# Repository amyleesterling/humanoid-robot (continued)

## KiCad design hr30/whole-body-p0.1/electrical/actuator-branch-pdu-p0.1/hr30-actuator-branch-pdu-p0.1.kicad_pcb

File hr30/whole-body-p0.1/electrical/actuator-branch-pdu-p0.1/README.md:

# HR-30 actuator branch PDU P0.1

**PRELIMINARY - NOT APPROVED FOR PROCUREMENT, FABRICATION, ASSEMBLY, CONNECTION, POWERED TESTING, MOTION OR ENERGIZATION**

This package provides one editable six-channel native KiCad schematic and routed 150 x 78 mm ten-layer PCB candidate. Five assembly instances allocate 25 whole-body actuator branches and retain five DNP spares. KiCad verifies schematic ERC 0/0, PCB DRC 0/0 and zero unconnected pads. The route separates shared input, individual outputs and six control-net families; exact production stackup, copper weight, DFM, thermal rise and physical tests remain open. It is a restrained commissioning architecture only; reverse energy, connector closure, dynamic torque and all work authority remain open.

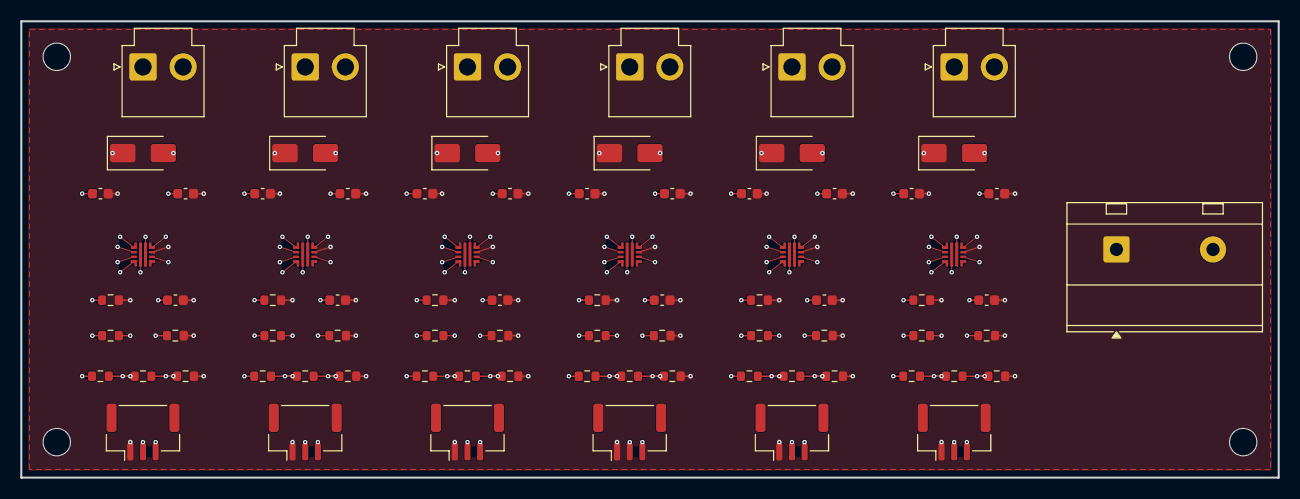
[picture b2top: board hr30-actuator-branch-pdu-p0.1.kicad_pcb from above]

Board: 10 copper layers, 124.0 x 45.0 mm, 83 parts (0 on the bottom side), 44 nets.

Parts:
C101, C201, C301, C401, C501, C601: 1uF 25V X7R input; C_0603_1608Metric
C102, C202, C302, C402, C502, C602: 2x1uF 25V X7R output equivalent; C_0603_1608Metric
C103, C203, C303, C403, C503, C603: 3.3nF dVdt; C_0603_1608Metric
D101, D201, D301, D401, D501, D601: LOCAL BRANCH CLAMP - DNP; D_SMA
J1: 12 V CONTROLLED INPUT; TerminalBlock_MetzConnect_Type703_RT10N02HGLU_1x02_P9.52mm_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
J101: CHANNEL 1 OUTPUT; JST_VH_B2P-VH_1x02_P3.96mm_Vertical
J102: CHANNEL 2 OUTPUT; JST_VH_B2P-VH_1x02_P3.96mm_Vertical
J103: CHANNEL 3 OUTPUT; JST_VH_B2P-VH_1x02_P3.96mm_Vertical
J104: CHANNEL 4 OUTPUT; JST_VH_B2P-VH_1x02_P3.96mm_Vertical
J105: CHANNEL 5 OUTPUT; JST_VH_B2P-VH_1x02_P3.96mm_Vertical
J106: CHANNEL 6 OUTPUT; JST_VH_B2P-VH_1x02_P3.96mm_Vertical
J201: CHANNEL 1 CONTROL; JST_GH_BM03B-GHS-TBT_1x03-1MP_P1.25mm_Vertical
J202: CHANNEL 2 CONTROL; JST_GH_BM03B-GHS-TBT_1x03-1MP_P1.25mm_Vertical
J203: CHANNEL 3 CONTROL; JST_GH_BM03B-GHS-TBT_1x03-1MP_P1.25mm_Vertical
J204: CHANNEL 4 CONTROL; JST_GH_BM03B-GHS-TBT_1x03-1MP_P1.25mm_Vertical
J205: CHANNEL 5 CONTROL; JST_GH_BM03B-GHS-TBT_1x03-1MP_P1.25mm_Vertical
J206: CHANNEL 6 CONTROL; JST_GH_BM03B-GHS-TBT_1x03-1MP_P1.25mm_Vertical
MH1, MH2, MH3, MH4: M2.5 BOARD-ONLY; MountingHole_2.7mm_M2.5
R101, R201, R301, R401, R501, R601: 470k 1% UVLO top; R_0603_1608Metric
R102, R202, R302, R402, R502, R602: 27.4k 1% UVLO/OVLO middle; R_0603_1608Metric
R103, R203, R303, R403, R503, R603: 40.2k 1% OVLO bottom; R_0603_1608Metric
R104, R204, R304, R404, R504, R604: 47k 1% PGTH top; R_0603_1608Metric
R105, R205, R305, R405, R505, R605: 5.76k 1% PGTH bottom; R_0603_1608Metric
R106, R206, R306, R406, R506, R606: ASSEMBLY VARIANT RILM; R_0603_1608Metric
U201, U202, U203, U204, U205, U206: TPS259474LRPWR circuit-breaker latch-off eFuse; TI_RPW0010A_HotRodQFN_2x2mm_P0.45mm_TI4225183A_P02

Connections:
BRANCH_1_12V: C102.1, D101.2, J101.2, R104.1, U201.6
BRANCH_2_12V: C202.1, D201.2, J102.2, R204.1, U202.6
BRANCH_3_12V: C302.1, D301.2, J103.2, R304.1, U203.6
BRANCH_4_12V: C402.1, D401.2, J104.2, R404.1, U204.6
BRANCH_5_12V: C502.1, D501.2, J105.2, R504.1, U205.6
BRANCH_6_12V: C602.1, D601.2, J106.2, R604.1, U206.6
CH1_DVDT: C103.1, U201.7
CH1_EN: J201.2, R101.2, R102.1, U201.1
CH1_ILM: R106.1, U201.9
CH1_OV: R102.2, R103.1, U201.2
CH1_PG: J201.3, U201.3
CH1_PGTH: R104.2, R105.1, U201.4
CH2_DVDT: C203.1, U202.7
CH2_EN: J202.2, R201.2, R202.1, U202.1
CH2_ILM: R206.1, U202.9
CH2_OV: R202.2, R203.1, U202.2
CH2_PG: J202.3, U202.3
CH2_PGTH: R204.2, R205.1, U202.4
CH3_DVDT: C303.1, U203.7
CH3_EN: J203.2, R301.2, R302.1, U203.1
CH3_ILM: R306.1, U203.9
CH3_OV: R302.2, R303.1, U203.2
CH3_PG: J203.3, U203.3
CH3_PGTH: R304.2, R305.1, U203.4
CH4_DVDT: C403.1, U204.7
CH4_EN: J204.2, R401.2, R402.1, U204.1
CH4_ILM: R406.1, U204.9
CH4_OV: R402.2, R403.1, U204.2
CH4_PG: J204.3, U204.3
CH4_PGTH: R404.2, R405.1, U204.4
CH5_DVDT: C503.1, U205.7
CH5_EN: J205.2, R501.2, R502.1, U205.1
CH5_ILM: R506.1, U205.9
CH5_OV: R502.2, R503.1, U205.2
CH5_PG: J205.3, U205.3
CH5_PGTH: R504.2, R505.1, U205.4
CH6_DVDT: C603.1, U206.7
CH6_EN: J206.2, R601.2, R602.1, U206.1
CH6_ILM: R606.1, U206.9
CH6_OV: R602.2, R603.1, U206.2
CH6_PG: J206.3, U206.3
CH6_PGTH: R604.2, R605.1, U206.4
PDU_0V: C101.2, C102.2, C103.2, C201.2, C202.2, C203.2, C301.2, C302.2, C303.2, C401.2, C402.2, C403.2, C501.2, C502.2, C503.2, C601.2, C602.2, C603.2, D101.1, D201.1, D301.1, D401.1, D501.1, D601.1, J1.1, J101.1, J102.1, J103.1, J104.1, J105.1, J106.1, J201.1, J202.1, J203.1, J204.1, J205.1, J206.1, R103.2, R105.2, R106.2, R203.2, R205.2, R206.2, R303.2, R305.2, R306.2, R403.2, R405.2, R406.2, R503.2, R505.2, R506.2, R603.2, R605.2, R606.2, U201.8, U202.8, U203.8, U204.8, U205.8, U206.8
PDU_12V_IN: C101.1, C201.1, C301.1, C401.1, C501.1, C601.1, J1.2, R101.1, R201.1, R301.1, R401.1, R501.1, R601.1, U201.5, U202.5, U203.5, U204.5, U205.5, U206.5

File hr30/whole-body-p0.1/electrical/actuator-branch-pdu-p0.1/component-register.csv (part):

reference,manufacturer,manufacturer_part_number,value,footprint,fitted_on_bare_six_channel_pattern,source,evidence,status,warning
J1,Phoenix Contact,MKDS 5/2-9.5 1714971,12 V CONTROLLED INPUT,TerminalBlock_MetzConnect:TerminalBlock_MetzConnect_Type703_RT10N02HGLU_1x02_P9.52mm_Horizontal,YES,https://www.phoenixcontact.com/en-us/products/pcb-terminal-b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,Phoenix 1714971 electrical candidate; temporary library outline has exact 9.52 mm pitch but body/holes require vendor-footprint verification,CANDIDATE / PHYSICAL VALIDATION OPEN,"PRELIMINARY - NOT APPROVED FOR PROCUREMENT, FABRICATION, ASSEMBLY, CONNECTION, POWERED TESTING, MOTION OR ENERGIZATION"
U201,Texas Instruments,TPS259474LRPWR,TPS259474LRPWR circuit-breaker latch-off eFuse,ProjectButton_RPW:TI_RPW0010A_HotRodQFN_2x2mm_P0.45mm_TI4225183A_P02,YES,https://www.ti.com/lit/ds/symlink/tps25947.pdf,SLVSFC9C Rev C May 2026; adjustable OVLO; circuit breaker; latch-off; PG/PGTH; reverse blocking,CANDIDATE / PHYSICAL VALIDATION OPEN,"PRELIMINARY - NOT APPROVED FOR PROCUREMENT, FABRICATION, ASSEMBLY, CONNECTION, POWERED TESTING, MOTION OR ENERGIZATION"
J101,JST,B2P-VH,CHANNEL 1 OUTPUT,Connector_JST:JST_VH_B2P-VH_1x02_P3.96mm_Vertical,YES,https://www.jst-mfg.com/product/pdf/eng/eVH.pdf,JST VH catalog; B2P-VH header; VHR-2N housing; contact and conductor selection remains controlled,CANDIDATE / PHYSICAL VALIDATION OPEN,"PRELIMINARY - NOT APPROVED FOR PROCUREMENT, FABRICATION, ASSEMBLY, CONNECTION, POWERED TESTING, MOTION OR ENERGIZATION"
J201,JST,BM03B-GHS-TBT,CHANNEL 1 CONTROL,Connector_JST:JST_GH_BM03B-GHS-TBT_1x03-1MP_P1.25mm_Vertical,YES,https://www.jst-mfg.com/product/pdf/eng/eGH.pdf,per-channel GND / open-drain DISABLE / PG service boundary; zero safety credit,CANDIDATE / PHYSICAL VALIDATION OPEN,"PRELIMINARY - NOT APPROVED FOR PROCUREMENT, FABRICATION, ASSEMBLY, CONNECTION, POWERED TESTING, MOTION OR ENERGIZATION"
R101,Yageo candidate,RC0603FR-07470KL,470k 1% UVLO top,Resistor_SMD:R_0603_1608Metric,YES,https://www.ti.com/lit/ds/symlink/tps25947.pdf,candidate calculation; tolerance and physical threshold test required,CANDIDATE / PHYSICAL VALIDATION OPEN,"PRELIMINARY - NOT APPROVED FOR PROCUREMENT, FABRICATION, ASSEMBLY, CONNECTION, POWERED TESTING, MOTION OR ENERGIZATION"
R102,Yageo candidate,RC0603FR-0727K4L,27.4k 1% UVLO/OVLO middle,Resistor_SMD:R_0603_1608Metric,YES,https://www.ti.com/lit/ds/symlink/tps25947.pdf,candidate calculation; tolerance and physical threshold test required,CANDIDATE / PHYSICAL VALIDATION OPEN,"PRELIMINARY - NOT APPROVED FOR PROCUREMENT, FABRICATION, ASSEMBLY, CONNECTION, POWERED TESTING, MOTION OR ENERGIZATION"
R103,Yageo candidate,RC0603FR-0740K2L,40.2k 1% OVLO bottom,Resistor_SMD:R_0603_1608Metric,YES,https://www.ti.com/lit/ds/symlink/tps25947.pdf,candidate calculation; tolerance and physical threshold test required,CANDIDATE / PHYSICAL VALIDATION OPEN,"PRELIMINARY - NOT APPROVED FOR PROCUREMENT, FABRICATION, ASSEMBLY, CONNECTION, POWERED TESTING, MOTION OR ENERGIZATION"
R104,Yageo candidate,RC0603FR-0747KL,47k 1% PGTH top,Resistor_SMD:R_0603_1608Metric,YES,https://www.ti.com/lit/ds/symlink/tps25947.pdf,candidate calculation; tolerance and physical threshold test required,CANDIDATE / PHYSICAL VALIDATION OPEN,"PRELIMINARY - NOT APPROVED FOR PROCUREMENT, FABRICATION, ASSEMBLY, CONNECTION, POWERED TESTING, MOTION OR ENERGIZATION"
R105,Yageo candidate,RC0603FR-075K76L,5.76k 1% PGTH bottom,Resistor_SMD:R_0603_1608Metric,YES,https://www.ti.com/lit/ds/symlink/tps25947.pdf,candidate calculation; tolerance and physical threshold test required,CANDIDATE / PHYSICAL VALIDATION OPEN,"PRELIMINARY - NOT APPROVED FOR PROCUREMENT, FABRICATION, ASSEMBLY, CONNECTION, POWERED TESTING, MOTION OR ENERGIZATION"
R106,Yageo candidate,1.24k / 1.47k / 3.83k,ASSEMBLY VARIANT RILM,Resistor_SMD:R_0603_1608Metric,YES,https://www.ti.com/lit/ds/symlink/tps25947.pdf,candidate calculation; tolerance and physical threshold test required,CANDIDATE / PHYSICAL VALIDATION OPEN,"PRELIMINARY - NOT APPROVED FOR PROCUREMENT, FABRICATION, ASSEMBLY, CONNECTION, POWERED TESTING, MOTION OR ENERGIZATION"
C101,SELECTION REQUIRED,SELECTION REQUIRED,1uF 25V X7R input,Capacitor_SMD:C_0603_1608Metric,YES,https://www.ti.com/lit/ds/symlink/tps25947.pdf,"TI application equation; voltage bias, tolerance and transient validation open",CANDIDATE / PHYSICAL VALIDATION OPEN,"PRELIMINARY - NOT APPROVED FOR PROCUREMENT, FABRICATION, ASSEMBLY, CONNECTION, POWERED TESTING, MOTION OR ENERGIZATION"
C102,SELECTION REQUIRED,SELECTION REQUIRED,2x1uF 25V X7R output equivalent,Capacitor_SMD:C_0603_1608Metric,YES,https://www.ti.com/lit/ds/symlink/tps25947.pdf,"TI application equation; voltage bias, tolerance and transient validation open",CANDIDATE / PHYSICAL VALIDATION OPEN,"PRELIMINARY - NOT APPROVED FOR PROCUREMENT, FABRICATION, ASSEMBLY, CONNECTION, POWERED TESTING, MOTION OR ENERGIZATION"
C103,SELECTION REQUIRED,SELECTION REQUIRED,3.3nF dVdt,Capacitor_SMD:C_0603_1608Metric,YES,https://www.ti.com/lit/ds/symlink/tps25947.pdf,"TI application equation; voltage bias, tolerance and transient validation open",CANDIDATE / PHYSICAL VALIDATION OPEN,"PRELIMINARY - NOT APPROVED FOR PROCUREMENT, FABRICATION, ASSEMBLY, CONNECTION, POWERED TESTING, MOTION OR ENERGIZATION"
D101,SELECTION REQUIRED,SELECTION REQUIRED,LOCAL BRANCH CLAMP - DNP,Diode_SMD:D_SMA,NO / DNP,https://www.ti.com/lit/ds/symlink/tps25947.pdf,"placeholder only; pulse energy, clamp voltage and regeneration architecture unresolved",CANDIDATE / PHYSICAL VALIDATION OPEN,"PRELIMINARY - NOT APPROVED FOR PROCUREMENT, FABRICATION, ASSEMBLY, CONNECTION, POWERED TESTING, MOTION OR ENERGIZATION"
U202,Texas Instruments,TPS259474LRPWR,TPS259474LRPWR circuit-breaker latch-off eFuse,ProjectButton_RPW:TI_RPW0010A_HotRodQFN_2x2mm_P0.45mm_TI4225183A_P02,YES,https://www.ti.com/lit/ds/symlink/tps25947.pdf,SLVSFC9C Rev C May 2026; adjustable OVLO; circuit breaker; latch-off; PG/PGTH; reverse blocking,CANDIDATE / PHYSICAL VALIDATION OPEN,"PRELIMINARY - NOT APPROVED FOR PROCUREMENT, FABRICATION, ASSEMBLY, CONNECTION, POWERED TESTING, MOTION OR ENERGIZATION"
J102,JST,B2P-VH,CHANNEL 2 OUTPUT,Connector_JST:JST_VH_B2P-VH_1x02_P3.96mm_Vertical,YES,https://www.jst-mfg.com/product/pdf/eng/eVH.pdf,JST VH catalog; B2P-VH header; VHR-2N housing; contact and conductor selection remains controlled,CANDIDATE / PHYSICAL VALIDATION OPEN,"PRELIMINARY - NOT APPROVED FOR PROCUREMENT, FABRICATION, ASSEMBLY, CONNECTION, POWERED TESTING, MOTION OR ENERGIZATION"
J202,JST,BM03B-GHS-TBT,CHANNEL 2 CONTROL,Connector_JST:JST_GH_BM03B-GHS-TBT_1x03-1MP_P1.25mm_Vertical,YES,https://www.jst-mfg.com/product/pdf/eng/eGH.pdf,per-channel GND / open-drain DISABLE / PG service boundary; zero safety credit,CANDIDATE / PHYSICAL VALIDATION OPEN,"PRELIMINARY - NOT APPROVED FOR PROCUREMENT, FABRICATION, ASSEMBLY, CONNECTION, POWERED TESTING, MOTION OR ENERGIZATION"
R201,Yageo candidate,RC0603FR-07470KL,470k 1% UVLO top,Resistor_SMD:R_0603_1608Metric,YES,https://www.ti.com/lit/ds/symlink/tps25947.pdf,candidate calculation; tolerance and physical threshold test required,CANDIDATE / PHYSICAL VALIDATION OPEN,"PRELIMINARY - NOT APPROVED FOR PROCUREMENT, FABRICATION, ASSEMBLY, CONNECTION, POWERED TESTING, MOTION OR ENERGIZATION"
R202,Yageo candidate,RC0603FR-0727K4L,27.4k 1% UVLO/OVLO middle,Resistor_SMD:R_0603_1608Metric,YES,https://www.ti.com/lit/ds/symlink/tps25947.pdf,candidate calculation; tolerance and physical threshold test required,CANDIDATE / PHYSICAL VALIDATION OPEN,"PRELIMINARY - NOT APPROVED FOR PROCUREMENT, FABRICATION, ASSEMBLY, CONNECTION, POWERED TESTING, MOTION OR ENERGIZATION"
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
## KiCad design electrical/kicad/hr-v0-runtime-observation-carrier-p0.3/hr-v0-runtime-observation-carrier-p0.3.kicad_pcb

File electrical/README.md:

# Electrical release area

The independently reviewed preliminary native ECAD is stored at [`kicad/project-button-v2/`](kicad/project-button-v2/). A separate connected correction candidate is stored at [`kicad/project-button-v3/`](kicad/project-button-v3/).

Current electrical identifier: **Project Button Electrical V2.1**  
Native tool: **KiCad 10.0.5**  
Status: **PRELIMINARY—NOT APPROVED FOR ENERGIZATION**

The directory contains the root `.kicad_pro`, root and 14 child `.kicad_sch` sheets, project symbol library, schedules, BOM, unresolved-selection register, primary-source register, native validation outputs, and synchronized review exports. `SOURCE-MANIFEST.csv` records the authoritative file hashes.

This is connected preliminary ECAD, not a build release. Clean ERC establishes modeled connectivity and annotation only. Exact physical selections, pinouts, ratings, protection coordination, conductor sizing, released enclosure/panel drawings, functional-safety analysis, firmware, and physical fault tests remain unresolved. Do not fabricate, wire, or energize from this package. R64's separate [`panel/hr-v0-control-panel-p0.4/`](panel/hr-v0-control-panel-p0.4/) directory retains the corrected enclosure allocation and freezes Littelfuse `75920-01` only as the exact SD1 catalog candidate. It releases no cutout, conductor, lockout procedure, drilling, cutting, wiring, assembly, or energization work.

## Electrical V3-P1.12 correction candidate

V3 is a generated native KiCad candidate that addresses the V2.1 automatic-restart blocker and removes project-built mains wiring from the proposed HR-V0 architecture. It has one index and twelve child sheets, separate RESET and ARM stages, two PNOZ s4 devices, two watchdog-contact channels, an explicit calculated ISO1212DBQ feedback sheet, K1/K2 mirror contacts and series power poles, external adapters, separately protected actuator branches, and one exact central DYNAMIXEL star-injection board boundary.

Current generated counts are 76 component blocks, 296 modeled terminals, 103 native nets (64 named connected nets plus 39 deliberate auto-generated unconnected nets), 257 unique wire labels, 64 unresolved component/interface rows, and 10 deliberately unresolved `TBD-*` terminal designations. P1.2 replaced three undefined inline injection modules with one exact 18-terminal `INJ1` representation synchronized to the separate native `DXL-STAR-P0.1` project; P1.3 corrected the K1/K2 application record; P1.4 retains received-lot terminal control for RESET and ARM without inventing four terminal marks; P1.5 freezes exact amber H1 while replacing misleading `SAFE ELIGIBLE` and `+/-` labels with diagnostic-only wording and `TBD-HA/TBD-HB` project placeholders. P1.11 replaces the unsupported P1J conversion chain with the exact GlobTek `WR9QI1660YL4NKITR6B` factory-cord boundary and keeps `J24`, `F24`, received fit, protection and physical evidence on hold. P1.12 removes the invented installed `JDBG1`, freezes Pi GPIO17/header pin 11 and header pin 6 return, and limits watchdog debug access to TP15/TP16/TP2 while the cable, runtime, fixture and physical evidence remain open. U2D2 VDD is omitted; three actuator-positive rails remain isolated; common TTL data and return are explicit. The routed star board passes native ERC/DRC 0/0, but fabrication, harness, protection, connector-current, thermal, waveform, no-backfeed, received H1 evidence and qualified review remain open. KiCad 10.0.5 ERC reports 0 errors and 0 warnings; native netlist, thirteen-page PDF, and thirteen SVG exports succeed. Run:

```powershell
python tools/generate_hr_v0_electrical_v3.py --validate
python tools/check_hr_v0_electrical_v3.py
python tools/check_hr_v0_control_panel.py
"C:\Program Files\KiCad\10.0\bin\python.exe" tools/generate_hr_v0_dxl_star.py
"C:\Program Files\KiCad\10.0\bin\python.exe" tools/check_hr_v0_dxl_star.py
```

V3 remains **PRELIMINARY - NOT APPROVED FOR FABRICATION OR ENERGIZATION**. It has not yet received the independent review or physical evidence required to supersede V2.1.

The separate star-board source and synchronized review outputs are at [`kicad/hr-v0-dxl-star/`](kicad/hr-v0-dxl-star/). No Gerber, drill, placement, or assembly outputs are released.

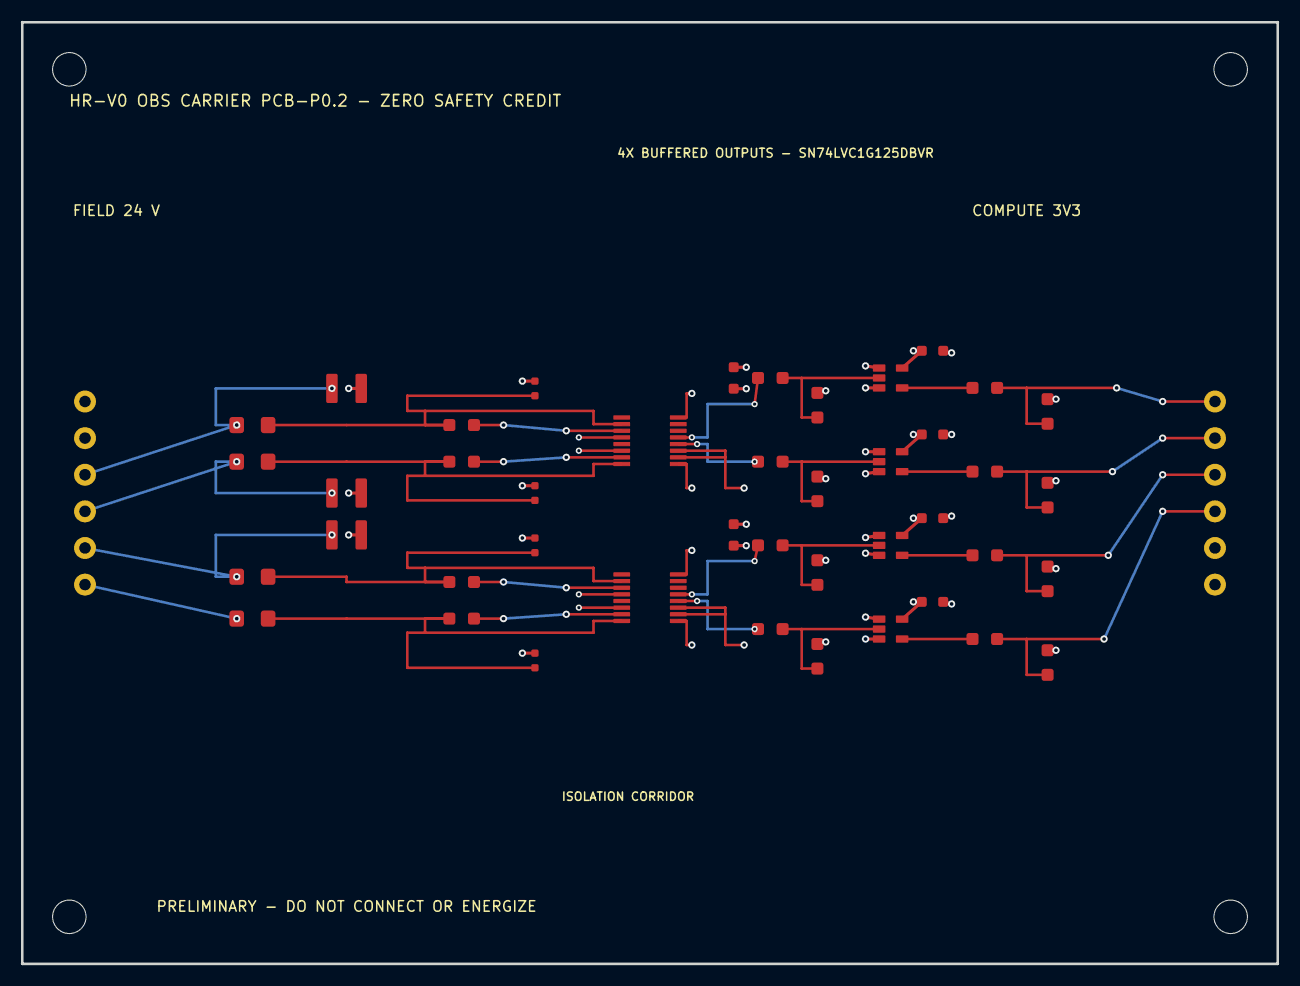
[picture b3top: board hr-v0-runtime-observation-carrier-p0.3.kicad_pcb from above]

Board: 4 copper layers, 120.0 x 90.0 mm, 49 parts (0 on the bottom side), 31 nets.

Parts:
CDEC1, CDEC2: Murata_GRM21_Reflow_Nominal
CDEC3, CDEC4, CDEC5, CDEC6: 100 nF 50 V X7R; Murata GRM21BR71H104KA01L; Murata_GRM21_Reflow_Nominal
CFI1, CFI2, CFI3, CFI4: TDK_CGA3_Reflow_Nominal
JFIELD1: Phoenix_MKDS_1_6_3P5_1751280
JLOGIC1: Phoenix_MKDS_1_6_3P5_1751280
MH1, MH2, MH3, MH4: BOARD-ONLY M3; HARDWARE/ENCLOSURE SELECTION REQUI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; MountingHole_3.2mm_M3
RGP1, RGP2, RGP3, RGP4: 36.5 kohm 1% 0.125 W 0805; Panasonic ERJ6ENF3652V; Panasonic_ERJ6_Reflow_Nominal
RPD1, RPD2, RPD3, RPD4: 47.0 kohm 1% 0.125 W 0805; Panasonic ERJ6ENF4702V; Panasonic_ERJ6_Reflow_Nominal
RPO1, RPO2, RPO3, RPO4: 330 kohm 1% 0.125 W 0805; Panasonic ERJ6ENF3303V; Panasonic_ERJ6_Reflow_Nominal
RSN1, RSN2, RSN3, RSN4: Panasonic_ERJ6_Reflow_Nominal
RSO1, RSO2, RSO3, RSO4: 1.50 kohm 1% 0.125 W 0805; Panasonic ERJ6ENF1501V; Panasonic_ERJ6_Reflow_Nominal
RTH1, RTH2, RTH3, RTH4: Vishay_MMA0204_IPC_Reflow
RW2, RW3, RW4: Vishay_CRCW1210_Reflow
UBUF1, UBUF2, UBUF3, UBUF4: Texas Instruments SN74LVC1G125DBVR; TI_DBV0005A_SOT23_5
UOBS1, UOBS2: TI_DBQ0016A_Example_Land

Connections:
COMPUTE_0V: CDEC1.2, CDEC2.2, CDEC3.2, CDEC4.2, CDEC5.2, CDEC6.2, JLOGIC1.2, RPD1.2, RPD2.2, RPD3.2, RPD4.2, RPO1.2, RPO2.2, RPO3.2, RPO4.2, UBUF1.1, UBUF1.3, UBUF2.1, UBUF2.3, UBUF3.1, UBUF3.3, UBUF4.1, UBUF4.3, UOBS1.1, UOBS1.8, UOBS2.1, UOBS2.8
K1_IN: RSN3.2, UOBS2.15
K1_SENSE: CFI3.1, RSN3.1, RTH3.2, UOBS2.16
K1_STATUS: JFIELD1.3, RTH3.1, RW3.1
K2_IN: RSN4.2, UOBS2.11
K2_SENSE: CFI4.1, RSN4.1, RTH4.2, UOBS2.10
K2_STATUS: JFIELD1.4, RTH4.1, RW4.1
OBS_K1_BUF_IN: RPD3.1, RSO3.2, UBUF3.2
OBS_K1_BUF_OUT: RGP3.1, UBUF3.4
OBS_K1_PI: JLOGIC1.5, RGP3.2, RPO3.1
OBS_K1_RAW: RSO3.1, UOBS2.4
OBS_K2_BUF_IN: RPD4.1, RSO4.2, UBUF4.2
OBS_K2_BUF_OUT: RGP4.1, UBUF4.4
OBS_K2_PI: JLOGIC1.6, RGP4.2, RPO4.1
OBS_K2_RAW: RSO4.1, UOBS2.5
OBS_SR1_BUF_IN: RPD1.1, RSO1.2, UBUF1.2
OBS_SR1_BUF_OUT: RGP1.1, UBUF1.4
OBS_SR1_PI: JLOGIC1.3, RGP1.2, RPO1.1
OBS_SR1_RAW: RSO1.1, UOBS1.4
OBS_SRA1_BUF_IN: RPD2.1, RSO2.2, UBUF2.2
OBS_SRA1_BUF_OUT: RGP2.1, UBUF2.4
OBS_SRA1_PI: JLOGIC1.4, RGP2.2, RPO2.1
OBS_SRA1_RAW: RSO2.1, UOBS1.5
PI_3V3_CANDIDATE: CDEC1.1, CDEC2.1, CDEC3.1, CDEC4.1, CDEC5.1, CDEC6.1, JLOGIC1.1, UBUF1.5, UBUF2.5, UBUF3.5, UBUF4.5, UOBS1.2, UOBS1.3, UOBS2.2, UOBS2.3
SAFETY_0V: CFI1.2, CFI2.2, CFI3.2, CFI4.2, JFIELD1.5, RW2.2, RW3.2, RW4.2, UOBS1.12, UOBS1.14, UOBS2.12, UOBS2.14
SR1_IN: RSN1.2, UOBS1.15
SR1_SENSE: CFI1.1, RSN1.1, RTH1.2, UOBS1.16
SR1_STATUS: JFIELD1.1, RTH1.1
SRA1_IN: RSN2.2, UOBS1.11
SRA1_SENSE: CFI2.1, RSN2.1, RTH2.2, UOBS1.10
SRA1_STATUS: JFIELD1.2, RTH2.1, RW2.1

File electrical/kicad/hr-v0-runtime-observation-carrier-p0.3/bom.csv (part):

reference,value,quantity,state,warning
JFIELD1,"Phoenix Contact MKDS 1/6-3,5 item 1751280",1,EXACT PCB TERMINAL CANDIDATE - PHYSICAL HOLD,"PRELIMINARY - NOT APPROVED FOR PROCUREMENT, FABRICATION, ASSEMBLY, CONNECTION, POWERED TESTING, MOTION, OR ENERGIZATION"
JLOGIC1,"Phoenix Contact MKDS 1/6-3,5 item 1751280",1,EXACT PCB TERMINAL CANDIDATE - PI/HARNESS/PHYSICAL HOLD,"PRELIMINARY - NOT APPROVED FOR PROCUREMENT, FABRICATION, ASSEMBLY, CONNECTION, POWERED TESTING, MOTION, OR ENERGIZATION"
RTH1,1.00 kohm 1% 0.4 W MELF; Vishay MMA02040C1001FB300,1,EXACT COMPONENT CANDIDATE - APPLICATION/PCB/PHYSICAL HOLD,"PRELIMINARY - NOT APPROVED FOR PROCUREMENT, FABRICATION, ASSEMBLY, CONNECTION, POWERED TESTING, MOTION, OR ENERGIZATION"
RSN1,562 ohm 1% 0.125 W 0805; Panasonic ERJ6ENF5620V,1,EXACT COMPONENT CANDIDATE - APPLICATION/PCB/PHYSICAL HOLD,"PRELIMINARY - NOT APPROVED FOR PROCUREMENT, FABRICATION, ASSEMBLY, CONNECTION, POWERED TESTING, MOTION, OR ENERGIZATION"
CFI1,10 nF 50 V X7R; TDK CGA3E2X7R1H103K080AA,1,EXACT COMPONENT CANDIDATE - DC-BIAS/PCB/EMC HOLD,"PRELIMINARY - NOT APPROVED FOR PROCUREMENT, FABRICATION, ASSEMBLY, CONNECTION, POWERED TESTING, MOTION, OR ENERGIZATION"
UOBS1,Texas Instruments ISO1212DBQ dual isolated digital-input receiver,1,EXACT IC CANDIDATE - PCB/EMC/FAULT/PHYSICAL HOLD,"PRELIMINARY - NOT APPROVED FOR PROCUREMENT, FABRICATION, ASSEMBLY, CONNECTION, POWERED TESTING, MOTION, OR ENERGIZATION"
RTH2,1.00 kohm 1% 0.4 W MELF; Vishay MMA02040C1001FB300,1,EXACT COMPONENT CANDIDATE - APPLICATION/PCB/PHYSICAL HOLD,"PRELIMINARY - NOT APPROVED FOR PROCUREMENT, FABRICATION, ASSEMBLY, CONNECTION, POWERED TESTING, MOTION, OR ENERGIZATION"
RSN2,562 ohm 1% 0.125 W 0805; Panasonic ERJ6ENF5620V,1,EXACT COMPONENT CANDIDATE - APPLICATION/PCB/PHYSICAL HOLD,"PRELIMINARY - NOT APPROVED FOR PROCUREMENT, FABRICATION, ASSEMBLY, CONNECTION, POWERED TESTING, MOTION, OR ENERGIZATION"
CFI2,10 nF 50 V X7R; TDK CGA3E2X7R1H103K080AA,1,EXACT COMPONENT CANDIDATE - DC-BIAS/PCB/EMC HOLD,"PRELIMINARY - NOT APPROVED FOR PROCUREMENT, FABRICATION, ASSEMBLY, CONNECTION, POWERED TESTING, MOTION, OR ENERGIZATION"
RW2,2.70 kohm 1% 0.5 W 1210; Vishay CRCW12102K70FKEA,1,EXACT COMPONENT CANDIDATE - APPLICATION/PCB/PHYSICAL HOLD,"PRELIMINARY - NOT APPROVED FOR PROCUREMENT, FABRICATION, ASSEMBLY, CONNECTION, POWERED TESTING, MOTION, OR ENERGIZATION"
RTH3,1.00 kohm 1% 0.4 W MELF; Vishay MMA02040C1001FB300,1,EXACT COMPONENT CANDIDATE - APPLICATION/PCB/PHYSICAL HOLD,"PRELIMINARY - NOT APPROVED FOR PROCUREMENT, FABRICATION, ASSEMBLY, CONNECTION, POWERED TESTING, MOTION, OR ENERGIZATION"
RSN3,562 ohm 1% 0.125 W 0805; Panasonic ERJ6ENF5620V,1,EXACT COMPONENT CANDIDATE - APPLICATION/PCB/PHYSICAL HOLD,"PRELIMINARY - NOT APPROVED FOR PROCUREMENT, FABRICATION, ASSEMBLY, CONNECTION, POWERED TESTING, MOTION, OR ENERGIZATION"
CFI3,10 nF 50 V X7R; TDK CGA3E2X7R1H103K080AA,1,EXACT COMPONENT CANDIDATE - DC-BIAS/PCB/EMC HOLD,"PRELIMINARY - NOT APPROVED FOR PROCUREMENT, FABRICATION, ASSEMBLY, CONNECTION, POWERED TESTING, MOTION, OR ENERGIZATION"
RW3,2.70 kohm 1% 0.5 W 1210; Vishay CRCW12102K70FKEA,1,EXACT COMPONENT CANDIDATE - APPLICATION/PCB/PHYSICAL HOLD,"PRELIMINARY - NOT APPROVED FOR PROCUREMENT, FABRICATION, ASSEMBLY, CONNECTION, POWERED TESTING, MOTION, OR ENERGIZATION"
UOBS2,Texas Instruments ISO1212DBQ dual isolated digital-input receiver,1,EXACT IC CANDIDATE - PCB/EMC/FAULT/PHYSICAL HOLD,"PRELIMINARY - NOT APPROVED FOR PROCUREMENT, FABRICATION, ASSEMBLY, CONNECTION, POWERED TESTING, MOTION, OR ENERGIZATION"
RTH4,1.00 kohm 1% 0.4 W MELF; Vishay MMA02040C1001FB300,1,EXACT COMPONENT CANDIDATE - APPLICATION/PCB/PHYSICAL HOLD,"PRELIMINARY - NOT APPROVED FOR PROCUREMENT, FABRICATION, ASSEMBLY, CONNECTION, POWERED TESTING, MOTION, OR ENERGIZATION"
RSN4,562 ohm 1% 0.125 W 0805; Panasonic ERJ6ENF5620V,1,EXACT COMPONENT CANDIDATE - APPLICATION/PCB/PHYSICAL HOLD,"PRELIMINARY - NOT APPROVED FOR PROCUREMENT, FABRICATION, ASSEMBLY, CONNECTION, POWERED TESTING, MOTION, OR ENERGIZATION"
CFI4,10 nF 50 V X7R; TDK CGA3E2X7R1H103K080AA,1,EXACT COMPONENT CANDIDATE - DC-BIAS/PCB/EMC HOLD,"PRELIMINARY - NOT APPROVED FOR PROCUREMENT, FABRICATION, ASSEMBLY, CONNECTION, POWERED TESTING, MOTION, OR ENERGIZATION"
RW4,2.70 kohm 1% 0.5 W 1210; Vishay CRCW12102K70FKEA,1,EXACT COMPONENT CANDIDATE - APPLICATION/PCB/PHYSICAL HOLD,"PRELIMINARY - NOT APPROVED FOR PROCUREMENT, FABRICATION, ASSEMBLY, CONNECTION, POWERED TESTING, MOTION, OR ENERGIZATION"
RSO1,1.50 kohm 1% 0.125 W 0805; Panasonic ERJ6ENF1501V,1,EXACT COMPONENT CANDIDATE - APPLICATION/PCB/PHYSICAL HOLD,"PRELIMINARY - NOT APPROVED FOR PROCUREMENT, FABRICATION, ASSEMBLY, CONNECTION, POWERED TESTING, MOTION, OR ENERGIZATION"
RPD1,47.0 kohm 1% 0.125 W 0805; Panasonic ERJ6ENF4702V,1,EXACT COMPONENT CANDIDATE - APPLICATION/PCB/PHYSICAL HOLD,"PRELIMINARY - NOT APPROVED FOR PROCUREMENT, FABRICATION, ASSEMBLY, CONNECTION, POWERED TESTING, MOTION, OR ENERGIZATION"
RGP1,36.5 kohm 1% 0.125 W 0805; Panasonic ERJ6ENF3652V,1,EXACT COMPONENT CANDIDATE - APPLICATION/PCB/PHYSICAL HOLD,"PRELIMINARY - NOT APPROVED FOR PROCUREMENT, FABRICATION, ASSEMBLY, CONNECTION, POWERED TESTING, MOTION, OR ENERGIZATION"
RPO1,330 kohm 1% 0.125 W 0805; Panasonic ERJ6ENF3303V,1,EXACT COMPONENT CANDIDATE - APPLICATION/PCB/PHYSICAL HOLD,"PRELIMINARY - NOT APPROVED FOR PROCUREMENT, FABRICATION, ASSEMBLY, CONNECTION, POWERED TESTING, MOTION, OR ENERGIZATION"
RSO2,1.50 kohm 1% 0.125 W 0805; Panasonic ERJ6ENF1501V,1,EXACT COMPONENT CANDIDATE - APPLICATION/PCB/PHYSICAL HOLD,"PRELIMINARY - NOT APPROVED FOR PROCUREMENT, FABRICATION, ASSEMBLY, CONNECTION, POWERED TESTING, MOTION, OR ENERGIZATION"
RPD2,47.0 kohm 1% 0.125 W 0805; Panasonic ERJ6ENF4702V,1,EXACT COMPONENT CANDIDATE - APPLICATION/PCB/PHYSICAL HOLD,"PRELIMINARY - NOT APPROVED FOR PROCUREMENT, FABRICATION, ASSEMBLY, CONNECTION, POWERED TESTING, MOTION, OR ENERGIZATION"
RGP2,36.5 kohm 1% 0.125 W 0805; Panasonic ERJ6ENF3652V,1,EXACT COMPONENT CANDIDATE - APPLICATION/PCB/PHYSICAL HOLD,"PRELIMINARY - NOT APPROVED FOR PROCUREMENT, FABRICATION, ASSEMBLY, CONNECTION, POWERED TESTING, MOTION, OR ENERGIZATION"
RPO2,330 kohm 1% 0.125 W 0805; Panasonic ERJ6ENF3303V,1,EXACT COMPONENT CANDIDATE - APPLICATION/PCB/PHYSICAL HOLD,"PRELIMINARY - NOT APPROVED FOR PROCUREMENT, FABRICATION, ASSEMBLY, CONNECTION, POWERED TESTING, MOTION, OR ENERGIZATION"
RSO3,1.50 kohm 1% 0.125 W 0805; Panasonic ERJ6ENF1501V,1,EXACT COMPONENT CANDIDATE - APPLICATION/PCB/PHYSICAL HOLD,"PRELIMINARY - NOT APPROVED FOR PROCUREMENT, FABRICATION, ASSEMBLY, CONNECTION, POWERED TESTING, MOTION, OR ENERGIZATION"
RPD3,47.0 kohm 1% 0.125 W 0805; Panasonic ERJ6ENF4702V,1,EXACT COMPONENT CANDIDATE - APPLICATION/PCB/PHYSICAL HOLD,"PRELIMINARY - NOT APPROVED FOR PROCUREMENT, FABRICATION, ASSEMBLY, CONNECTION, POWERED TESTING, MOTION, OR ENERGIZATION"
RGP3,36.5 kohm 1% 0.125 W 0805; Panasonic ERJ6ENF3652V,1,EXACT COMPONENT CANDIDATE - APPLICATION/PCB/PHYSICAL HOLD,"PRELIMINARY - NOT APPROVED FOR PROCUREMENT, FABRICATION, ASSEMBLY, CONNECTION, POWERED TESTING, MOTION, OR ENERGIZATION"
RPO3,330 kohm 1% 0.125 W 0805; Panasonic ERJ6ENF3303V,1,EXACT COMPONENT CANDIDATE - APPLICATION/PCB/PHYSICAL HOLD,"PRELIMINARY - NOT APPROVED FOR PROCUREMENT, FABRICATION, ASSEMBLY, CONNECTION, POWERED TESTING, MOTION, OR ENERGIZATION"
RSO4,1.50 kohm 1% 0.125 W 0805; Panasonic ERJ6ENF1501V,1,EXACT COMPONENT CANDIDATE - APPLICATION/PCB/PHYSICAL HOLD,"PRELIMINARY - NOT APPROVED FOR PROCUREMENT, FABRICATION, ASSEMBLY, CONNECTION, POWERED TESTING, MOTION, OR ENERGIZATION"
RPD4,47.0 kohm 1% 0.125 W 0805; Panasonic ERJ6ENF4702V,1,EXACT COMPONENT CANDIDATE - APPLICATION/PCB/PHYSICAL HOLD,"PRELIMINARY - NOT APPROVED FOR PROCUREMENT, FABRICATION, ASSEMBLY, CONNECTION, POWERED TESTING, MOTION, OR ENERGIZATION"
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
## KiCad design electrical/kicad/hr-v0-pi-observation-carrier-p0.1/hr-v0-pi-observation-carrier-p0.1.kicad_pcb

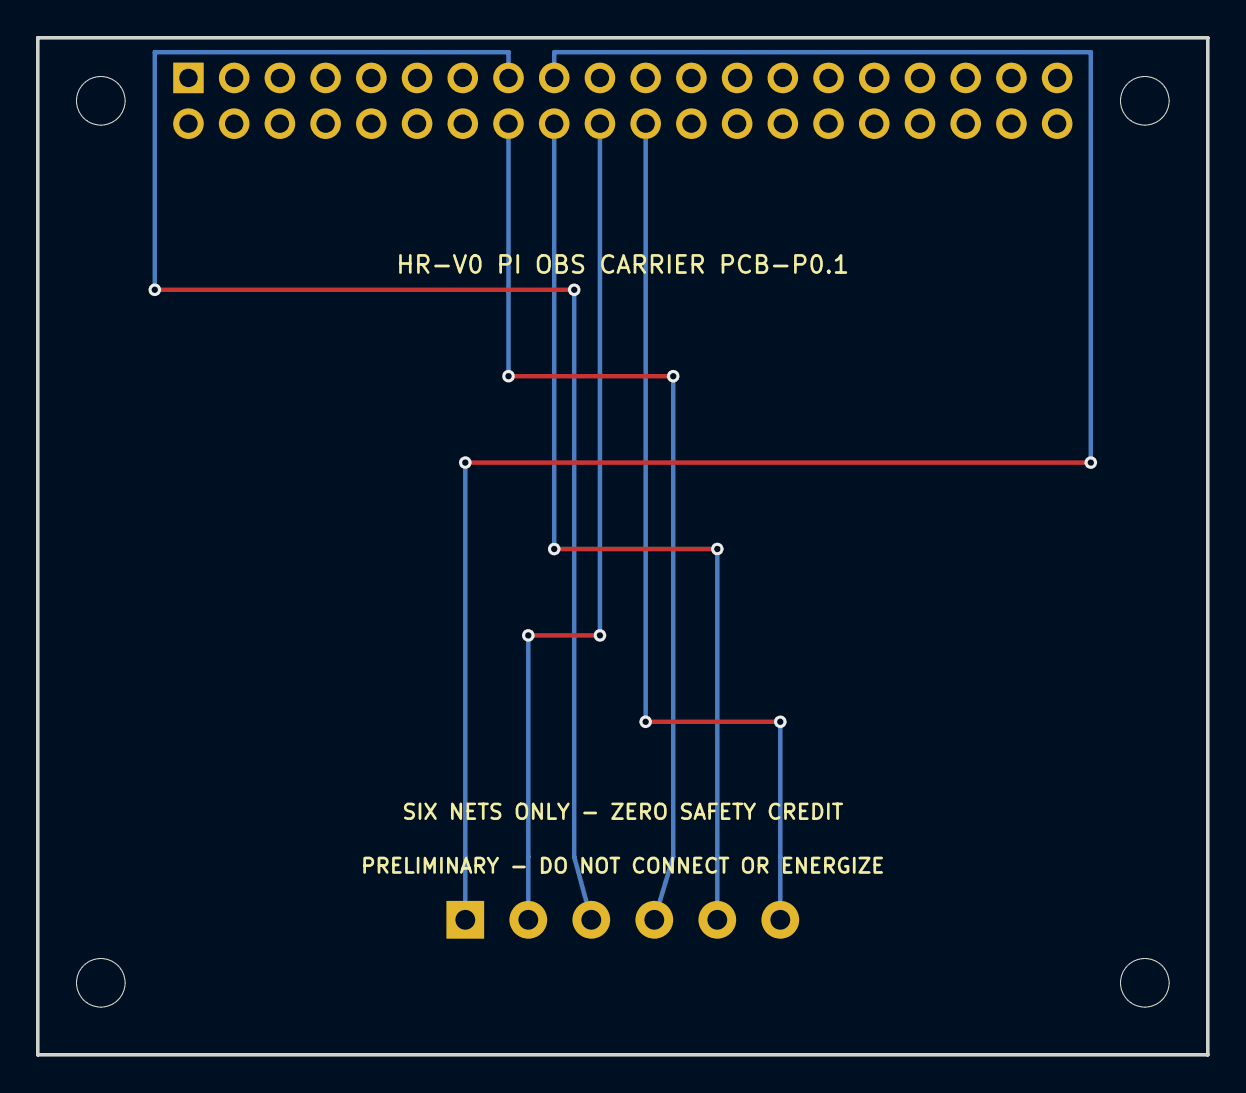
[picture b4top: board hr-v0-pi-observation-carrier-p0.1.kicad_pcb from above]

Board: 2 copper layers, 65.0 x 56.5 mm, 6 parts (0 on the bottom side), 6 nets.

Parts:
JOBS1: Phoenix_MKDS_1_6_3P5_1751280
JPI1: Samtec_ESQ_120_33_G_D
MH1, MH2, MH3, MH4: BOARD-ONLY REFERENCE HOLE; RECEIVED FIT/HARDWARE 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; MountingHole_2.7mm_M2.5

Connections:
COMPUTE_0V: JOBS1.2, JPI1.20
OBS_K1_PI: JOBS1.5, JPI1.18
OBS_K2_PI: JOBS1.6, JPI1.22
OBS_SR1_PI: JOBS1.3, JPI1.15
OBS_SRA1_PI: JOBS1.4, JPI1.16
PI_3V3_CANDIDATE: JOBS1.1, JPI1.17

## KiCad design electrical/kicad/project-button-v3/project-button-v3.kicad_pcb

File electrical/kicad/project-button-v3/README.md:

# Project Button HR-V0 Electrical V3-P1.14

**PRELIMINARY - NOT APPROVED FOR FABRICATION OR ENERGIZATION**

This is a generated, connected native KiCad candidate derived from `tools/generate_hr_v0_electrical_v3.py`. It does not supersede the reviewed Electrical V2.1 package until exact selections, application reviews, calculations, physical tests and qualified review close.

## Pages

1. `01_external_sources.kicad_sch` — External listed sources and DC boundaries
2. `02_estop_eligibility.kicad_sch` — Dual-channel E-stop and RESET eligibility
3. `03_arm_watchdog_eligibility.kicad_sch` — Distinct ARM and watchdog-gated SR1 supply
4. `04_contactor_edm.kicad_sch` — Contactor coils, mirror contacts and EDM
5. `05_actuator_interruption.kicad_sch` — Redundant actuator-power interruption
6. `06_branches_and_injection.kicad_sch` — Protected actuator branches and central DYNAMIXEL star injection
7. `07_watchdog_control.kicad_sch` — Independent watchdog power, controller and drivers
8. `08_watchdog_feedback_interface.kicad_sch` — Calculated dual-channel 24 V watchdog feedback
9. `09_compute_and_control_terminals.kicad_sch` — Compute and control terminals
10. `10_actuator_interfaces.kicad_sch` — U2D2, actuator ports and bonding boundary
11. `11_watchdog_pcb_connectors.kicad_sch` — Watchdog PCB external connectors
12. `12_watchdog_pcb_test_access.kicad_sch` — Watchdog PCB test access

## Material corrections relative to V2.1

- Separate SR1 RESET eligibility and SRA1 ARM/EDM stages.
- Two separately driven ordinary watchdog relay contacts are in series with the SR1 A1 supply. Heartbeat loss power-cycles SR1 and forces the physical RESET stage to drop, while S0 remains direct in both SR1 input loops. Internal KWD A1/21-to-14 shorts can defeat the diagnostic gate but cannot inject downstream of S0. Supply switching, protected routing, common-cause analysis and physical proof remain open; the watchdog receives zero safety credit.
- Phoenix relay terminals are frozen from the official circuit diagram. Both 24 V NC diagnostics pass through the calculated ISO1212DBQ input network before the Pico GPIO. Exact proposed passive order codes are frozen; PCB, received measurements, derating and physical validation remain open.
- Compute heartbeat crosses an exact VO618A-4X017T optical interface with exact 910 Ohm input and 10 kOhm pullup candidates. Two separate TPL7407LPWR packages drive the two relay coils, with unused inputs tied low, unused outputs open, and local 100 nF COM bypass candidates. These ordinary circuits receive no safety credit and still require PCB, timing, hot-plug, fault-injection, EMC and qualified review.
- The ISO1212 feedback network uses exact proposed Vishay, Panasonic, TDK and Murata passive order codes. Receiving, PCB land-pattern/placement, DC-bias, pulse, thermal, EMC, fault and HIL evidence remain mandatory.
- Three exact Phoenix Contact PCB terminal-block candidates freeze the project pin allocation for 24 V/control return, two coil sinks, two NC feedback channels and the isolated heartbeat pair. Harness, conductor, ferrule, protection, enclosure, received-orientation and thermal evidence remain open.
- `project-button-v3.kicad_pcb` is the native PCB-P0.9 routed/test-access candidate. It is geometry/topology-identical to PCB-P0.8 and adds exact hidden manufacturer, MPN, assembly-description, process-class, no-alternate and process-state fields for all 42 populated references. It retains the deeper R138 document/land fields for UDRV1/UDRV2/UFB1/ISO1, the R89 manufacturer-traced lands and exact rectangular 3.45 x 1.85 mm Harwin issue-10 test-point copper. It encodes a 0.1524 mm minimum trace/clearance. Supplier-normalized XYRS and assembly process remain SELECTION REQUIRED. It is not a Gerber or fabrication release; supplier acceptance, installed probe access, protection coordination, schematic parity review, creepage/clearance, thermal, EMC and HIL evidence remain gates.
- Heartbeat restoration cannot restore contactors; SRA1 requires a new monitored ARM action.
- Factory-sealed external adapters replace project-built mains wiring; the 24 V candidate is GlobTek `WR9QI1660YL4NKITR6B` with its factory YL4/C40337 locking cord.
- The GST280A12-C6P source bond is explicit; project star point SP1 is DNP/prohibited.
- Three poles per candidate contactor are represented in series, pending Schneider application confirmation.
- U2D2 VDD is omitted and protected power is injected by one central DXL-STAR-P0.1 board with three isolated VDD branches; harness, thermal, waveform and no-backfeed evidence remain design gates.
- RESET `S1` and ARM `S2` retain exact complete IDEC order codes, but their physical terminals remain `TBD-*`. IDEC's 2026 production transition permits prior or redesigned internals under the same complete codes, and the live product BOM exposes no component identity. Only received-lot markings, orientation, continuity and independent comparison may release the terminal map.
- H1 is exact amber IDEC `HW1P-1FQD-A-24V`, labeled `RESET STAGE READY - DIAGNOSTIC ONLY / NO MOTION AUTHORITY`. The prior `SAFE ELIGIBLE` name and `+/-` pin implication are removed. `TBD-HA/TBD-HB` are project placeholders pending received terminal, internal-circuit, polarity/current, brightness and human-factors evidence; H1 receives no safety credit.

## Validate

Run `python tools/generate_hr_v0_electrical_v3.py --validate` with KiCad 10 installed. Generated ERC proves only modeled connectivity/annotation. Every `TBD-*`, `SELECTION REQUIRED`, `DESIGN REQUIRED`, and application-confirmation item remains a release blocker.

No drawing in this directory authorizes ordering, wiring, fabrication or energization.

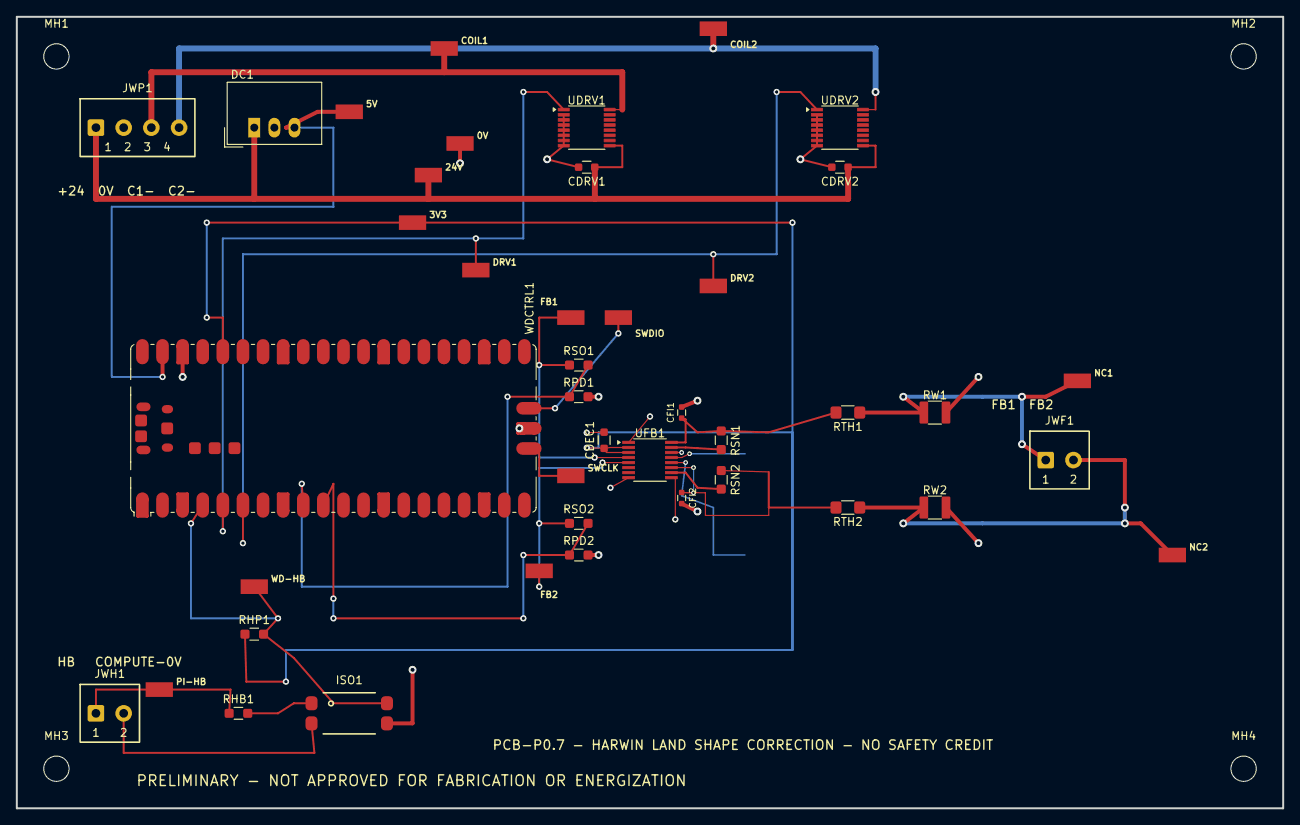
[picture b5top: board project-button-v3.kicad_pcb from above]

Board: 2 copper layers, 160.0 x 100.0 mm, 46 parts (0 on the bottom side), 24 nets.

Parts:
CDEC1: Murata GRM21BR71H104KA01L, 100 nF 50 V X7R 0805; Murata_GRM21_Reflow_Nominal
CDRV1, CDRV2: Murata GRM21BR71H104KA01L, 100 nF 50 V X7R 0805; Murata_GRM21_Reflow_Nominal
CFI1, CFI2: TDK CGA3E2X7R1H103K080AA, 10 nF 50 V X7R 0603; TDK_CGA3_Reflow_Nominal
DC1: TRACO POWER TSR 1-2450, 24 V to 5 V 1 A non-isola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; Converter_DCDC_TRACO_TSR-1_THT
ISO1: Vishay VO618A-4X017T heartbeat optocoupler; VO618A_Option7_SMD
JWF1: Phoenix Contact MKDS 1/2-3,5, item 1751248; MKDS_1_2_3P5
JWH1: Phoenix Contact MKDS 1/2-3,5, item 1751248; MKDS_1_2_3P5
JWP1: Phoenix Contact MKDS 1/4-3,5, item 1751264; MKDS_1_4_3P5
MH1, MH2, MH3, MH4: M3 BOARD-ONLY - MOUNTING/ENCLOSURE SELECTION OPEN; MountingHole_3.2mm_M3
RHB1: Panasonic ERJ6ENF9100V, 910 Ohm 1% 0805 0.125 W; Panasonic_ERJ6_Reflow_Nominal
RHP1: Panasonic ERJ6ENF1002V, 10.0 kOhm 1% 0805 0.125 W; Panasonic_ERJ6_Reflow_Nominal
RPD1, RPD2: Panasonic ERJ6ENF1002V, 10.0 kOhm 1% 0805; Panasonic_ERJ6_Reflow_Nominal
RSN1, RSN2: Panasonic ERJ6ENF5620V, 562 Ohm 1% 0805; Panasonic_ERJ6_Reflow_Nominal
RSO1, RSO2: Panasonic ERJ6ENF1001V, 1.00 kOhm 1% 0805; Panasonic_ERJ6_Reflow_Nominal
RTH1, RTH2: Vishay MMA02040C1001FB300, 1.00 kOhm 1% 0.4 W MELF; Vishay_MMA0204_IPC_Reflow
RW1, RW2: Vishay CRCW12102K70FKEA, 2.70 kOhm 1% 0.5 W 1210; Vishay_CRCW1210_Reflow
TP1, TP2, TP3, TP4, TP5, TP6, TP7, TP8, TP9, TP10, TP11, TP12, TP13, TP14, TP15, TP16: Harwin S1751-46R SMT test point; Harwin_S1751_46R
UDRV1: Texas Instruments TPL7407LPWR channel-1 relay dri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; TI_PW0016A_Example_Land
UDRV2: Texas Instruments TPL7407LPWR channel-2 relay dri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; TI_PW0016A_Example_Land
UFB1: Texas Instruments ISO1212DBQ dual 24 V input rece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; TI_DBQ0016A_Example_Land
WDCTRL1: Raspberry Pi Pico 1, order SC0915 / RP2040; RaspberryPi_Pico_SMD

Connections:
COMPUTE_0V: ISO1.2, JWH1.2
FB_IN1: RSN1.2, UFB1.15
FB_IN2: RSN2.2, UFB1.10
FB_SENSE1: CFI1.1, RSN1.1, RTH1.2, UFB1.16
FB_SENSE2: CFI2.1, RSN2.1, RTH2.2, UFB1.11
HB_LED_A: ISO1.1, RHB1.2
PI_HEARTBEAT: JWH1.1, RHB1.1, TP5.1
SAFETY_0V: CDEC1.2, CDRV1.2, CDRV2.2, CFI1.2, CFI2.2, DC1.2, ISO1.3, JWP1.2, RPD1.2, RPD2.2, RW1.2, RW2.2, TP2.1, UDRV1.2, UDRV1.3, UDRV1.4, UDRV1.5, UDRV1.6, UDRV1.7, UDRV1.8, UDRV2.2, UDRV2.3, UDRV2.4, UDRV2.5, UDRV2.6, UDRV2.7, UDRV2.8, UFB1.1, UFB1.8, UFB1.9, UFB1.14, WDCTRL1.38, WDCTRL1.D2
SAFETY_24V: CDRV1.1, CDRV2.1, DC1.1, JWP1.1, TP1.1, UDRV1.9, UDRV2.9
UFB_OUT1: RSO1.1, TP13.1, UFB1.4
UFB_OUT2: RSO2.1, TP14.1, UFB1.5
WD1_COIL_N: JWP1.3, TP9.1, UDRV1.16
WD1_DRIVE: TP7.1, UDRV1.1, WDCTRL1.5
WD1_NC_24V: JWF1.1, RTH1.1, RW1.1, TP11.1
WD1_NC_DIAG: RPD1.1, RSO1.2, WDCTRL1.9
WD2_COIL_N: JWP1.4, TP10.1, UDRV2.16
WD2_DRIVE: TP8.1, UDRV2.1, WDCTRL1.6
WD2_NC_24V: JWF1.2, RTH2.1, RW2.1, TP12.1
WD2_NC_DIAG: RPD2.1, RSO2.2, WDCTRL1.10
WD_3V3: CDEC1.1, RHP1.1, TP4.1, UFB1.2, UFB1.3, WDCTRL1.36
WD_5V: DC1.3, TP3.1, WDCTRL1.39
WD_HEARTBEAT: ISO1.4, RHP1.2, TP6.1, WDCTRL1.4
WD_SWCLK: TP16.1, WDCTRL1.D1
WD_SWDIO: TP15.1, WDCTRL1.D3
